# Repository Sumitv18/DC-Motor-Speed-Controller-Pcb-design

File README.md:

# DC-Motor-Speed-Controller-Pcb-design

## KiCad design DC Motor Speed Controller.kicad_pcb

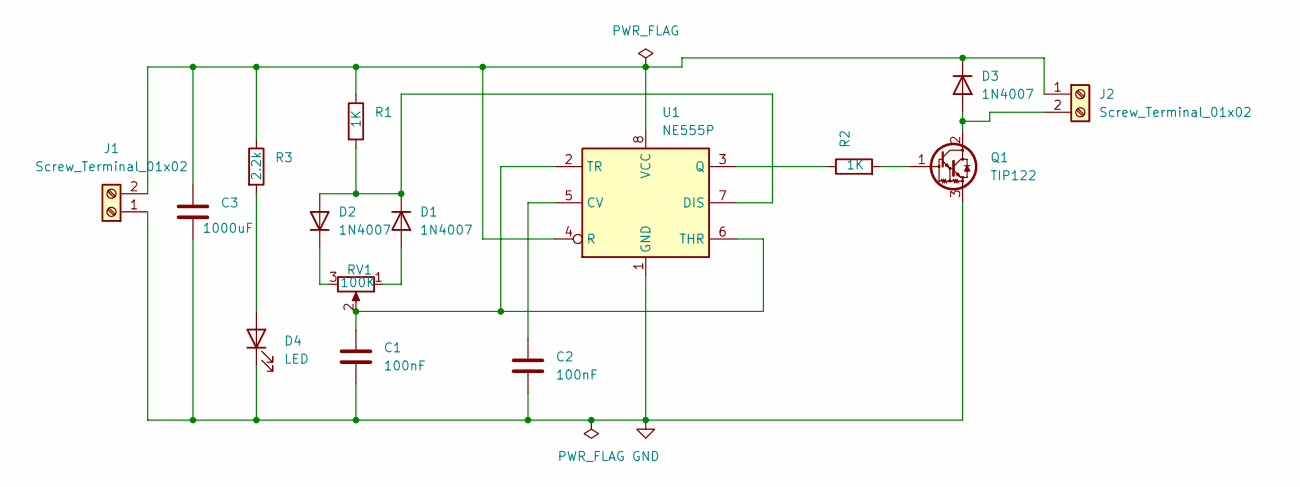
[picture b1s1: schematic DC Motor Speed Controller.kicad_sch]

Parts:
C1, C2: 100nF; C_Disc_D4.7mm_W2.5mm_P5.00mm
C3: 1000uF; C_Rect_L7.0mm_W4.5mm_P5.00mm
D1, D2, D3: 1N4007; D_DO-41_SOD81_P10.16mm_Horizontal
D4: LED; LED_D5.0mm
J1, J2: Screw_Terminal_01x02; TerminalBlock_bornier-2_P5.08mm
Q1: TIP122; TO-220-3_Vertical
R1, R2: 1K; R_Axial_DIN0204_L3.6mm_D1.6mm_P7.62mm_Horizontal
R3: 2.2k; R_Axial_DIN0204_L3.6mm_D1.6mm_P7.62mm_Horizontal
RV1: 100K; Potentiometer_Alps_RK163_Single_Horizontal
U1: NE555P; DIP-8_W7.62mm

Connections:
GND: C1.2, C2.2, C3.2, D4.1 (K), J1.1, Q1.3 (E), U1.1 (GND)
unnamed: D1.2 (A), RV1.1
unnamed: D1.1 (K), D2.2 (A), R1.2, U1.7 (DIS)
unnamed: D2.1 (K), RV1.3
unnamed: D3.2 (A), J2.2, Q1.2 (C)
unnamed: C3.1, D3.1 (K), J1.2, J2.1, R1.1, R3.1, U1.4 (R), U1.8 (VCC)
unnamed: D4.2 (A), R3.2
unnamed: Q1.1 (B), R2.2
unnamed: C2.1, U1.5 (CV)
unnamed: R2.1, U1.3 (Q)
unnamed: C1.1, RV1.2, U1.2 (TR), U1.6 (THR)

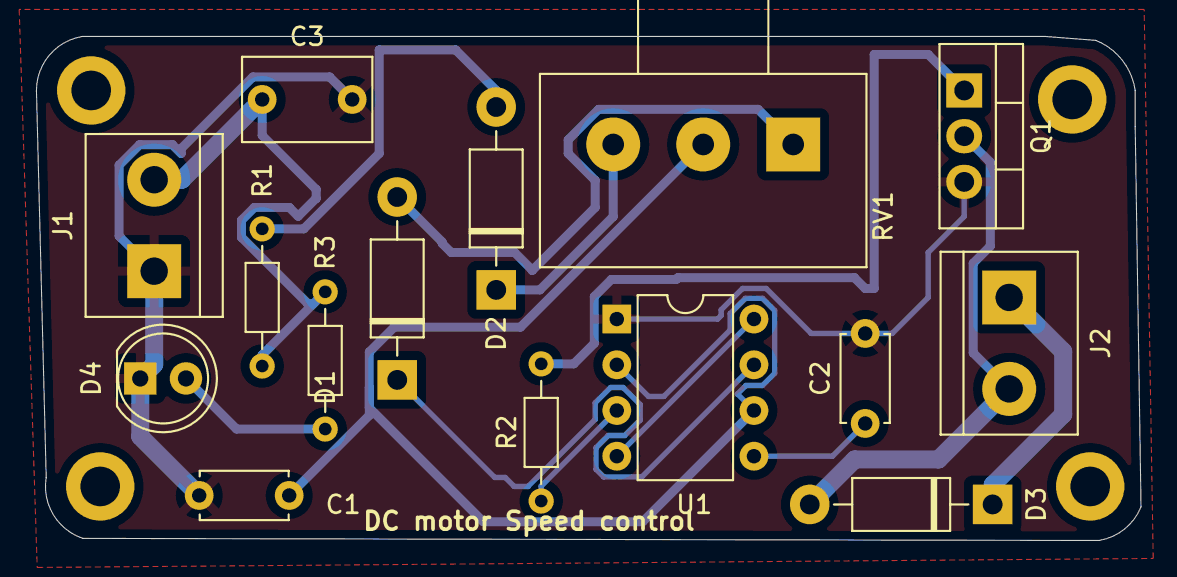
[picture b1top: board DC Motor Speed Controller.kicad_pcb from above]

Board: 2 copper layers, 61.4 x 28.0 mm, 15 parts (0 on the bottom side), 11 nets.
